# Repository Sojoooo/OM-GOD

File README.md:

<h1 align="center">
  <br>
  OM-GOD
  <br>
</h1>

<h4 align="center">
Ominichord [Gate of Divinity]. Mash-up of all the previous omnichords and more.
</h4>

<div align="center">

</div>

<p align="center">
  <a href="#key-features">Key Features</a> •
  <a href="#design-process">Design Process</a> •
  <a href="#pcb">PCB</a> •
  <a href="#bom">BOM</a> •
  <a href="#journal">Development Journal</a> •
  <a href="#credits">Credits</a> •
  <a href="#license">License</a>
</p>

## Key Features

- **STM32H7 microcontroller** for high-performance processing
- **Texas Instruments DACs and amplifiers** for professional audio quality
- **MIDI connectivity** for external device integration
- **USB-C programming and power delivery**
- **Battery-powered portable design**
- **Cherry MX mechanical switches** for tactile feedback
- **48-button chord matrix** (4 rows × 12 buttons)
- **Rotary encoders** for parameter control
- **LED display** for status and settings

## Design Process

The OM-GOD project began with extensive research into existing omnichord designs and their features. After compiling schematics and manuals, I created a comprehensive feature list to guide the development process.

## PCB

Designed in KiCad with a focus on audio quality and modern features. Notable components:

- **STM32H7** microcontroller with 144 GPIO pins
- **PCM5122PW DAC** for high-quality audio conversion
- **TPA3116D2DAD Class D amplifier** for powerful audio output
- **BQ24610** battery charging circuit for portable operation
- **Multiple voltage regulators** (12V, 15V, 5V, 3.3V)
- **USB-C power delivery** with negotiator circuit
- **NFC antenna** for contactless communication

### Schematic Development

The schematic evolved through multiple iterations, starting with basic component selection and progressing to a complete audio system with power management, I/O interfaces, and user controls.

### Component Integration

Key integration challenges included:

- Audio signal buffering for noise reduction
- Power distribution for multiple voltage rails
- Component placement optimization
- Signal integrity considerations

### PCB

The PCB layout was made to ensure a proper audio quality. All analog traces  and chips are on the bottom layer, while digital traces are on the top. Also, the gnd plane in the inner bottom layer acts as a faraday's cage, not letting them interfier with each other.

### Final Design

The final design incorporates all planned features while maintaining a compact, portable form factor suitable for live performance.

## BOM

| Component  | Source        | Cost (USD)  |
| ---------  | ------        | ----------- |
| PCB        | JLCPCB        | $348.25     |
| SPEAKER    | MERCADO LIBRE | $7.00       |
| FLEX CABLE | MERCADO LIBRE | $4.42       |
| JST CABLE  | MERCADO LIBRE | $5.00       |
| **Total**  |               | **364.67** |

_Note: Speakers, keycaps, and case are already owned components from previous projects._

## Credits

This project uses:

- [KiCad](https://www.kicad.org/) - PCB design
- [STM32](https://www.st.com/en/microcontrollers-microprocessors/stm32h7-series.html) - Microcontroller
- [Texas Instruments](https://www.ti.com/) - Audio and power components
- [Fusion 360](https://www.autodesk.com/products/fusion-360/) - 3D modeling

## License

MIT

---

> GitHub [@Sojooo](https://github.com/Sojooo)

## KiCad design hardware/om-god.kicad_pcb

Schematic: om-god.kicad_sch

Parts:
AUDIO1: PJ-393_C2837065; AUDIO-SMD_PJ-393; LCSC Part C2837065
C1, C2, C3, C7, C12, C17, C34, C35, C36, C37, C38, C39, C81, C188, C196: 2.2uF; C_0402_1005Metric
C4, C5, C6, C8, C9, C10, C11, C13, C14, C15, C16, C18, C40, C42, C43, C44, C45, C50, C51, C52, C53, C54, C55, C59, C60, C61, C62, C63, C75, C76, C79, C80, C83, C84, C124, C126, C127, C130, C133, C134, C138, C139, C141, C147, C150, C152, C153, C156, C158, C163, C198, C199, C200, C201, C202, C203, C206: 0.1uF; C_0402_1005Metric
C19, C20, C21, C22, C23, C24, C25, C26, C27, C28, C29, C30, C31, C32, C33: 10uF; CAP-SMD_BD4.0-L4.3-W4.3-FD
C41, C117: 0.1uF; C_0603_1608Metric
C46, C47: 82nF; C_Rect_L4.0mm_W2.5mm_P2.50mm
C48, C49, C64, C65: 5.6nF; C_Rect_L4.0mm_W2.5mm_P2.50mm
C56, C57: 82nF; C_0603_1608Metric
C58: 100uF; C_0402_1005Metric
C66, C67, C68, C69, C70, C71, C72, C73, C82, C165, C189, C190, C191, C193, C194, C195, C197: 1uF; C_0402_1005Metric
C74: 10nF; C_0402_1005Metric
C77, C85, C86, C87, C88: 1nF; C_0402_1005Metric
C78, C97, C98, C99, C100, C140, C144, C145, C146, C151, C155, C159, C161, C164, C166, C172, C174, C175, C178: 100nF; C_0402_1005Metric
C89, C90, C91, C92, C93, C94, C95, C96, C185, C186, C187: 220nF; C_0402_1005Metric
C101, C102, C103, C104: 220uF; CP_Radial_D8.0mm_P3.50mm
C105, C106, C107, C108: 680nF; C_0603_1608Metric
C109, C110, C111, C112, C113, C114, C115, C116: 1uF; C_0603_1608Metric
C118, C119, C120, C121, C122, C123: 10nF; C_0603_1608Metric
C125: 2.2uF; CP_Radial_D8.0mm_P2.50mm
C128, C136, C148: 1uF; CP_Radial_D5.0mm_P2.00mm
C129, C132: 10uF; C_0402_1005Metric
C131: 0.1uF; CP_Radial_D5.0mm_P2.00mm
C137: 10uF; C_0402_1005Metric; not fitted
C142, C149: 220pF; C_0402_1005Metric
C143, C160, C162, C167: 10uF; CP_Radial_D8.0mm_P3.50mm
C154, C157: 22uF; C_0402_1005Metric
C168, C169: 5.1pF; C_0402_1005Metric
C170, C171: 5.6pF; C_0402_1005Metric
C173: 22pF; C_0402_1005Metric
C176, C177, C179, C180, C181, C184: 10uF; C_0603_1608Metric
C182, C183, C192: 220nF; C_0603_1608Metric
C204, C205, C210: 47pF; C_0402_1005Metric; not fitted
C207, C208, C209: 47pF; C_0603_1608Metric; not fitted
C211, C212, C213, C214, C215, C216, C217, C218, C219, C220, C221, C222, C223, C224, C225, C226, C227, C228, C229, C230, C231, C232, C233, C234: 22uF; C_0603_1608Metric
CN1, CN2: DIN-504B-M10; CONN-TH_DIN-504B-M10; LCSC Part C2939346
Card1: TF PUSH; TF-SMD_TF-PUSH; LCSC Part C393941
D1, D2, D3, D4, D5, D6, D7, D8, D9, D10, D11, D12, D13, D14, D15, D16, D17, D18, D19, D20, D21, D22, D23, D24, D25, D26, D27, D28, D29, D30, D31, D32, D33, D34, D35, D36, D37, D38, D39, D40, D41, D42, D43, D44, D45, D46, D47, D48: 1N4148WS_C917117; SOD-323_L1.8-W1.3-LS2.5-RD; LCSC Part C917117
D49: LED; LED0603-RD; LCSC C5656657
D50: 1N4148WT; D_SOD-523
D51: PESD15VL1BA; D_SOD-323_TVS
D52, D53, D54: LED; LED_0603_1608Metric
D55: BAT54; SOT-23
FPC1: 5034801200; FPC-SMD_5034801200; LCSC Part C587969
J1, J2, J5: PJ-625G; AUDIO-TH_PJ-625G; LCSC Part C309300
J3: Conn_01x13_Pin; PinHeader_1x13_P2.54mm_Vertical
J4: Conn_01x03_Pin; PinHeader_1x03_P2.54mm_Vertical
J6, J10: Conn_01x08_Pin; CONN-TH_B8PS-VH-LF-SN; LCSC C157970
J7, J8, J9, J11: Conn_01x02_Socket; CONN-TH_2P-P5.00_WJ500V-5.08-2P; LCSC C8465
L1, L2, L3, L4, L5, L6: 10uH; IND-SMD_L11.0-W10.5_SL1050-330M
L7: 27uH; IND-SMD_L4.8-W3.4
L8: EXC14CE900U; FILTER-SMD_4P-L0.9-W0.7-P0.50-BL; LCSC Part C178761
L9: 6.8uH; L_6.3x6.3_H3
L10: 8uH; L1206
L11, L15: 6.8uH; IND-SMD_L3.2-W2.5_L3225
L12, L13, L14: 15uH; IND-SMD_L12.3-W12.3
OC1: H11L1; DIP-6_W7.62mm_LongPads
Q1, Q2, Q3: Si7617DN; Vishay_PowerPAK_1212-8_Single
R1, R2, R3, R4, R5, R6: 470K; R_0402_1005Metric
R7, R8, R12, R13, R14, R15, R16, R17, R21, R22, R23, R25, R29, R30, R33, R34, R52, R58, R59, R60, R61, R62, R63, R79, R92, R93, R94, R115, R116: 10K; R_0402_1005Metric
R9, R10, R11, R19, R20, R24, R47, R48, R53, R55, R56, R57, R70, R71, R72: 6K; R_0402_1005Metric
R18: 5K; R_0402_1005Metric
R26: 33; R_0402_1005Metric
R27: 220; R_0402_1005Metric
R28, R84: 10; R_0402_1005Metric
R31, R32, R36, R37, R38, R39, R54, R77, R95, R117: 1K; R_0402_1005Metric
R35: 470; R_0402_1005Metric
R40, R42: 47k; R_0402_1005Metric
R41, R43: 75k; R_0402_1005Metric
R44, R45, R46, R49, R50: 100k; R_0402_1005Metric
R51, R109, R133, R135: 10k; R_0402_1005Metric
R64, R65, R66, R67, R68, R69: 3.3; R_0402_1005Metric
R73: 2; R_0402_1005Metric
R74, R75, R78, R80, R89, R110, R112, R121, R123, R125, R127, R129, R131: 100K; R_0402_1005Metric
R76: 32.4K; R_0402_1005Metric
R81: 22.1K; R_0402_1005Metric
R82, R105: 0.01; R_0402_1005Metric
R83, R87: 1k; R_0402_1005Metric
R85: 200K; R_0402_1005Metric
R86, R104: 1.5K; R_0402_1005Metric
R88: 9.31K; R_0402_1005Metric
R90: NTCG163JF103FT1S; R0603; LCSC Part C406719
R91: 430K; R_0402_1005Metric
R96, R97, R98, R99, R100, R101, R102, R103: 22; R_0402_1005Metric
R106: 49.9; R_0402_1005Metric
R107: 50k; R_0402_1005Metric
R108: 2.61k; R_0402_1005Metric
R111: 500K; R_0402_1005Metric
R113, R114: 0; R_0402_1005Metric
R122: 24.9K; R_0402_1005Metric
R124, R132: 43.2K; R_0402_1005Metric
R126, R128, R130: 9.09K; R_0402_1005Metric
R134: 4.7k; R_0402_1005Metric
SW1, SW2, SW3, SW4, SW6, SW7, SW8, SW9, SW11, SW12, SW13, SW14, SW15, SW16, SW17, SW18, SW21, SW22, SW23, SW24, SW25, SW26, SW27, SW28, SW29, SW30, SW31, SW32, SW35, SW36, SW37, SW38, SW39, SW40, SW41, SW42, SW43, SW44, SW45, SW46, SW47, SW48, SW49, SW50, SW51, SW52, SW53, SW54, SW55, SW56, SW57: TS-1003ST-26; SW-SMD_4P-L12.0-W12.0-P5.00-LS15.4; LCSC Part C455234
SW5, SW10, SW19, SW20, SW33, SW34: RotaryEncoder; SW-TH_EC12EXXXX; LCSC C470684
SW58, SW60: SW_Push; SW_SPST_CK_RS282G05A3
SW59: RotaryEncoder_Switch; SW-TH_EC11E1820402; LCSC C361165
U1, U2, U3: PCM5122PW; TSSOP-28_4.4x9.7mm_P0.65mm
U4, U5, U6, U7, U8, U11, U16, U20, U23: NE5532DR; SOIC-8_L4.9-W3.9-P1.27-LS6.0-BL; LCSC Part C7426
U9, U10, U12, U13, U14: SW-TH_6P-L7.0-W7.0-P2.00_7-7-ZS; LCSC C5379891
U15: TS5A23159RSER; UQFN-10_L2.0-W1.5-P0.50-BL-EP; LCSC Part C138710
U17: TPA6120A2DWP; HSOP-20_L12.8-W7.5-P1.27-LS10.3-BL-EP3.3; LCSC Part C2871054
U18, U19: TPA3116D2DAD_C2865736; HTSSOP-32_L11.0-W6.1-P0.65-LS8.1-BL; LCSC Part C2865736
U21: CY8CMBR3116-LQXIT; QFN-24_L4.0-W4.0-P0.50-BL-EP2.6; LCSC Part C914913
U22, U24: FPC-05F-6PH20; FPC-SMD_6P-P0.50_XUNPU_FPC-05F-6PH20; LCSC C2856796
U25: BQ24610; VQFN-24-1EP_4x4mm_P0.5mm_EP2.45x2.45mm
U26: TPS54202DDC; SOT-23-6
U27: W29N02KVSIAF; TSOP-48_L12.0-W18.4-P0.50-LS20.0-TL; LCSC C2940193
U28: USBLC6-2P6; SOT-666
U29: TUSB422IYFPR; DSBGA-9_L1.4-W1.3-R3-C3-P0.40-BL; LCSC Part C702378
U30, U31: SIS412DN-T1-GE3-ES; PDFN-8_L3.1-W3.1-P0.65-LS3.4-BL; LCSC Part C21713860
U32: CRYSTAL-SMD_4P-L3.2-W2.5-BL_SIT8008BI; LCSC C7294602
U33: HS20HS072RX; OLED-SMD_HS20HS072RX; LCSC Part C5329582
U34, U35, U36, U37, U38, U39: LMR33630ADDAR; ESOP-8_L4.9-W3.9-P1.27-LS6.0-TL-EP; LCSC Part C841384
USB1: TYPE-C 16PIN 2MD(073); USB-C-SMD_TYPE-C-6PIN-2MD-073; LCSC Part C2765186
VQ1: STM32H723ZGT6; LQFP-144_L20.0-W20.0-P0.50-LS22.0-BL; LCSC Part C730146
Y1: 32.768KHz; FC-135R_L3.2-W1.5

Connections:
3.3BATT: C191.2, C210.1, C218.1, C224.1, C230.1, C234.1, J6.8, J10.8, L15.2, R131.2, VQ1.6 (VBAT)
7th: D3.1 (C), D7.1 (C), D11.1 (C), D15.1 (C), D19.1 (C), D23.1 (C), D27.1 (C), D31.1 (C), D35.1 (C), D39.1 (C), D43.1 (C), D47.1 (C), VQ1.37 (PA3)
#CE: U27.9, VQ1.98 (PC8)
#RE: U27.8, VQ1.118 (PD4)
#WE: U27.18, VQ1.119 (PD5)
+3.3V: C5.1, C10.1, C15.1, C21.1, C26.1, C31.1, C58.1, C60.1, C80.1, C82.1, C134.2, C140.1, C141.1, C144.1, C146.1, C150.2, C151.1, C155.1, C159.1, C161.1, C164.1, C165.1, C166.1, C174.1, C175.1, C178.1, C198.2, C205.1, C212.1, C217.1, C223.1, C229.1, Card1.4 (VDD), FPC1.8, FPC1.9, FPC1.11, J6.5, J10.5, L11.2, OC1.6 (VCC), R18.2, R22.1, R23.1, R26.1, R29.2, R33.2, R35.2, R52.1, R58.2, R59.2, R60.2, R61.2, R62.2, R63.2, R75.2, R78.2, R80.2, R83.1, R85.1, R86.2, R87.1, R88.1, R104.1, R113.1, R123.2, SW58.2, SW60.2, U1.17 (MODE1), U1.28 (DVDD), U2.17 (MODE1), U2.28 (DVDD), U3.17 (MODE1), U3.28 (DVDD), U15.8 (VCC), U21.7 (VDD), U27.12, U27.34, U27.37, U27.39, U29.A3 (VDD), VQ1.17 (VDD), VQ1.30 (VDD), VQ1.39 (VDD), VQ1.52 (VDD), VQ1.62 (VDD), VQ1.72 (VDD), VQ1.84 (VDD), VQ1.95 (VDD33USB), VQ1.108 (VDD), VQ1.121 (VDD), VQ1.131 (VDD), VQ1.144 (VDD)
+3.3VA: C4.1, C8.1, C9.1, C13.1, C14.1, C18.1, C19.1, C23.1, C24.1, C28.1, C29.1, C33.1, C172.1, R113.2, R114.1, R114.2, U1.1 (CPVDD), U1.8 (AVDD), U1.25 (XSMT), U2.1 (CPVDD), U2.8 (AVDD), U2.25 (XSMT), U3.1 (CPVDD), U3.8 (AVDD), U3.25 (XSMT), VQ1.32 (VREF+), VQ1.33 (VDDA)
+5V: C204.1, C211.1, C216.1, C222.1, C228.1, J6.6, J10.6, L10.2, R121.2, R134.2
+12V: C41.2, C44.2, C45.2, C52.2, C54.2, C55.2, C61.1, C63.2, C74.1, C76.1, C84.2, C85.2, C86.2, C87.2, C88.2, C97.2, C98.2, C99.2, C100.2, C101.1, C102.1, C103.1, C104.1, C124.2, C129.1, C132.1, C133.1, C137.1, C139.1, C207.1, C208.1, C209.1, C213.1, C214.1, C215.1, C219.1, C220.1, C221.1, C225.1, C226.1, C227.1, C231.1, C232.1, C233.1, J6.1, J6.2, J10.1, J10.2, L12.2, L13.2, L14.2, R45.1, R46.1, R50.2, R125.2, R127.2, R129.2, U4.1 (VCC+), U5.1 (VCC+), U6.1 (VCC+), U7.1 (VCC+), U8.1 (VCC+), U11.1 (VCC+), U16.1 (VCC+), U17.3 (LVCC+), U17.18 (RVCC+), U18.17 (AVCC), U18.18 (PVCC), U18.19 (PVCC), U18.31 (PVCC), U18.32 (PVCC), U19.17 (AVCC), U19.18 (PVCC), U19.19 (PVCC), U19.31 (PVCC), U19.32 (PVCC), U20.1 (VCC+), U23.1 (VCC+), U26.3 (VIN)
+BATT: C158.1, C160.1, C162.1, C173.2, C184.1, C192.1, J11.1, Q3.5 (D), R105.2, R111.1, U25.13 (SRN), U39.2 (VIN), U39.3 (EN)
-12V: C40.2, C42.2, C43.2, C50.2, C51.2, C53.2, C59.2, C62.2, C75.2, C79.2, C117.2, C137.2, C139.2, C153.2, C154.2, C157.2, J6.7, J10.7, R108.1, U4.5 (VCC-), U5.5 (VCC-), U6.5 (VCC-), U7.5 (VCC-), U8.5 (VCC-), U11.5 (VCC-), U16.5 (VCC-), U17.1 (LVCC-), U17.20 (RVCC-), U20.5 (VCC-), U23.5 (VCC-), U26.1 (GND)
ALE: U27.17, VQ1.81 (PD12)
BCK HEADPHONE: U1.21 (BCK), VQ1.69 (PB10)
BCK SPEAKER: U2.21 (BCK), VQ1.41 (PA5)
BCK STEREO OUT: U3.21 (BCK), VQ1.133 (PB3)
CLE: U27.16, VQ1.80 (PD11)
Chord A: SW1.3, SW1.4, SW2.3, SW2.4, SW3.3, SW3.4, SW4.3, SW4.4, VQ1.7 (PC13)
Chord Ab: SW51.3, SW51.4, SW52.3, SW52.4, SW53.3, SW53.4, SW54.3, SW54.4, VQ1.28 (PC2_C)
Chord B: SW11.3, SW11.4, SW12.3, SW12.4, SW13.3, SW13.4, SW14.3, SW14.4, VQ1.13 (PF3)
Chord Bb: SW6.3, SW6.4, SW7.3, SW7.4, SW8.3, SW8.4, SW9.3, SW9.4, VQ1.12 (PF2)
Chord C: SW15.3, SW15.4, SW16.3, SW16.4, SW17.3, SW17.4, SW18.3, SW18.4, VQ1.14 (PF4)
Chord D: SW25.3, SW25.4, SW26.3, SW26.4, SW27.3, SW27.4, SW28.3, SW28.4, VQ1.18 (PF6)
Chord Db: SW21.3, SW21.4, SW22.3, SW22.4, SW23.3, SW23.4, SW24.3, SW24.4, VQ1.15 (PF5)
Chord E: SW35.3, SW35.4, SW36.3, SW36.4, SW37.3, SW37.4, SW38.3, SW38.4, VQ1.20 (PF8)
Chord Eb: SW29.3, SW29.4, SW30.3, SW30.4, SW31.3, SW31.4, SW32.3, SW32.4, VQ1.19 (PF7)
Chord F: SW39.3, SW39.4, SW40.3, SW40.4, SW41.3, SW41.4, SW42.3, SW42.4, VQ1.21 (PF9)
Chord G: SW47.3, SW47.4, SW48.3, SW48.4, SW49.3, SW49.4, SW50.3, SW50.4, VQ1.26 (PC0)
Chord Gb: SW43.3, SW43.4, SW44.3, SW44.4, SW45.3, SW45.4, SW46.3, SW46.4, VQ1.22 (PF10)
Chords Volume Encoder A: SW19.A, VQ1.127 (PG12)
Chords Volume Encoder B: SW19.B, VQ1.126 (PG11)
DIN HEADPHONE: U1.22 (DIN), VQ1.27 (PC1)
DIN SPEAKER: U2.22 (DIN), VQ1.43 (PA7)
DIN STEREO OUT: U3.22 (DIN), VQ1.48 (PB2)
DN USB: L8.1, U24.5
DN USB 2: U22.5, VQ1.103 (PA11)
DP USB: L8.2, U24.6
DP USB 2: U22.6, VQ1.104 (PA12)
Extention: D4.1 (C), D8.1 (C), D12.1 (C), D16.1 (C), D20.1 (C), D24.1 (C), D28.1 (C), D32.1 (C), D36.1 (C), D40.1 (C), D44.1 (C), D48.1 (C), VQ1.42 (PA6)
Func Encoder A: SW59.A, VQ1.87 (PG2)
Func Encoder B: SW59.B, VQ1.82 (PD13)
Func Switch: SW59.S1, VQ1.79 (PD10)
GND: AUDIO1.4, C4.2, C5.2, C6.1, C7.1, C8.2, C9.2, C10.2, C11.1, C12.1, C13.2, C14.2, C15.2, C16.1, C17.1, C18.2, C19.2, C20.2, C21.2, C22.2, C23.2, C24.2, C25.2, C26.2, C27.2, C28.2, C29.2, C30.2, C31.2, C32.2, C33.2, C34.2, C35.2, C36.2, C37.2, C38.2, C39.2, C40.1, C41.1, C42.1, C43.1, C44.1, C45.1, C48.1, C49.1, C50.1, C51.1, C52.1, C53.1, C54.1, C55.1, C56.1, C57.1, C58.2, C59.1, C60.2, C61.2, C62.1, C63.1, C66.2, C67.2, C74.2, C75.1, C76.2, C77.2, C78.1, C79.1, C80.2, C81.2, C82.2, C83.2, C84.1, C85.1, C86.1, C87.1, C88.1, C97.1, C98.1, C99.1, C100.1, C101.2, C102.2, C103.2, C104.2, C105.1, C106.2, C107.1, C108.2, C109.1, C110.2, C111.1, C112.2, C113.1, C114.2, C115.1, C116.2, C117.1, C118.1, C119.2, C120.1, C121.2, C122.1, C123.2, C124.1, C125.2, C127.1, C128.2, C129.2, C131.2, C132.2, C133.2, C134.1, C136.2, C138.2, C140.2, C141.2, C142.2, C143.2, C144.2, C145.2, C146.2, C148.2, C149.2, C150.1, C151.2, C153.1, C154.1, C155.2, C156.2, C157.1, C159.2, C160.2, C161.2, C162.2, C164.2, C165.2, C166.2, C167.2, C168.1, C169.1, C170.1, C171.1, C172.2, C174.2, C175.2, C176.2, C177.2, C178.2, C179.2, C180.2, C181.2, C182.2, C183.2, C184.2, C185.2, C186.2, C187.2, C188.2, C189.2, C190.2, C191.1, C192.2, C193.2, C194.2, C195.2, C196.2, C197.2, C198.1, C211.2, C212.2, C213.2, C214.2, C215.2, C216.2, C217.2, C218.2, C219.2, C220.2, C221.2, C222.2, C223.2, C224.2, C225.2, C226.2, C227.2, C228.2, C229.2, C230.2, C231.2, C232.2, C233.2, C234.2, CN1.6, CN1.7, CN2.2, CN2.6, CN2.7, Card1.6 (VSS), Card1.10, Card1.11, Card1.12, Card1.13, D49.1 (K), D51.1 (K), FPC1.1, FPC1.10, FPC1.12, FPC1.13, FPC1.14, J1.2, J2.2, J5.2, J6.3, J6.4, J10.3, J10.4, J11.2, L7.2, OC1.5 (GND), R10.2, R12.1, R14.1, R20.2, R30.1, R34.1, R36.1, R37.1, R41.2, R43.2, R44.2, R49.2, R53.2, R55.2, R70.2, R76.2, R79.2, R81.2, R90.2, R91.2, R106.2, R109.1, R112.2, R122.1, R124.1, R126.1, R128.1, R130.1, R132.1, R133.1, R135.1, SW5.C, SW10.C, SW19.C, SW20.C, SW33.C, SW34.C, SW55.1, SW55.2, SW56.3, SW56.4, SW57.3, SW57.4, SW59.C, SW59.S2, U1.3 (CPGND), U1.9 (AGND), U1.16 (ADR2/GPIO2/DOUT), U1.18 (MODE2/MS), U1.24 (ADR1/MISO/FMT), U1.27 (DGND), U2.3 (CPGND), U2.9 (AGND), U2.16 (ADR2/GPIO2/DOUT), U2.18 (MODE2/MS), U2.24 (ADR1/MISO/FMT), U2.27 (DGND), U3.3 (CPGND), U3.9 (AGND), U3.16 (ADR2/GPIO2/DOUT), U3.18 (MODE2/MS), U3.24 (ADR1/MISO/FMT), U3.27 (DGND), U4.4 (IN2+), U4.6 (IN1+), U8.4 (IN2+), U8.6 (IN1+), U9.5, U10.5, U12.5, U13.1, U14.1, U15.3 (GND), U17.21 (EP), U18.1 (MODSEL), U18.9 (GND), U18.13 (AM2), U18.14 (AM1), U18.15 (AM0), U18.22 (GND), U18.25 (GND), U18.28 (GND), U18.33 (PAD), U19.1 (MODSEL), U19.9 (GND), U19.10 (LINP), U19.11 (LINN), U19.13 (AM2), U19.14 (AM1), U19.15 (AM0), U19.22 (GND), U19.25 (GND), U19.28 (GND), U19.33 (PAD), U21.8 (VSS), U21.25 (EP), U22.4, U22.7, U22.8, U23.6 (IN1+), U24.4, U24.7, U24.8, U25.17 (GND), U25.25 (GND), U27.13, U27.25, U27.36, U27.48, U28.2 (GND), U29.C2 (GND), U30.1 (S), U30.2 (S), U30.3 (S), U32.2, U32.4, U34.1 (PGND), U34.9 (EP), U35.1 (PGND), U35.9 (EP), U36.1 (PGND), U36.9 (EP), U37.1 (PGND), U37.9 (EP), U38.1 (PGND), U38.9 (EP), U39.1 (PGND), U39.9 (EP), USB1.1 (GND), USB1.12 (GND), USB1.13 (SHELL), USB1.14 (SHELL), VQ1.16 (VSS), VQ1.31 (VSSA), VQ1.38 (VSS), VQ1.51 (VSS), VQ1.61 (VSS), VQ1.83 (VSS), VQ1.94 (VSS), VQ1.107 (VSS), VQ1.120 (VSS), VQ1.130 (VSS)
GPIO3 HEADPHONE: U1.15 (GPIO3/AGNS), VQ1.49 (PF11)
GPIO3 SPEAKER: U2.15 (GPIO3/AGNS), VQ1.57 (PG1)
GPIO3 STEREO OUT: U3.15 (GPIO3/AGNS), VQ1.44 (PC4)
GPIO4 HEADPHONE: U1.14 (GPIO4/MAST), VQ1.50 (PF12)
GPIO4 SPEAKER: U2.14 (GPIO4/MAST), VQ1.64 (PE11)
GPIO4 STEREO OUT: U3.14 (GPIO4/MAST), VQ1.45 (PC5)
GPIO5 HEADPHONE: U1.13 (GPIO5/ATT0), VQ1.53 (PF13)
GPIO5 SPEAKER: U2.13 (GPIO5/ATT0), VQ1.65 (PE12)
GPIO5 STEREO OUT: U3.13 (GPIO5/ATT0), VQ1.46 (PB0)
GPIO6 HEADPHONE: U1.19 (GPIO6/FLT), VQ1.56 (PG0)
GPIO6 SPEAKER: U2.19 (GPIO6/FLT), VQ1.66 (PE13)
GPIO6 STEREO OUT: U3.19 (GPIO6/FLT), VQ1.47 (PB1)
HEADPHONE AMP L: AUDIO1.2, R117.2, U17.2 (LOUT)
HEADPHONE AMP R: AUDIO1.3, R54.1, U17.19 (ROUT)
HEADPHONE BUFF L N: R11.1, R32.2, U5.2 (OUT2)
HEADPHONE BUFF L P: R9.2, R31.1, U5.7 (IN1-), U5.8 (OUT1)
HEADPHONE BUFF R N: R24.1, R39.2, U11.2 (OUT2)
HEADPHONE BUFF R P: R19.2, R38.1, U11.7 (IN1-), U11.8 (OUT1)
HEADPHONE DAC L: C34.1, R1.2, U5.6 (IN1+)
HEADPHONE DAC R: C35.1, R2.2, U11.6 (IN1+)
HEADPHONE GPIO L: AUDIO1.6, R29.1, VQ1.67 (PE14)
HEADPHONE GPIO R: AUDIO1.7, R33.1, VQ1.68 (PE15)
INT_N USB: R85.2, U24.3, U29.B2 (INT_N)
INT_N USB 2: U22.3, VQ1.102 (PA10)
IO0: R103.2, VQ1.85 (PD14)
IO1: R102.2, VQ1.86 (PD15)
IO2: R101.2, VQ1.114 (PD0)
IO3: R100.2, VQ1.115 (PD1)
IO4: R99.2, VQ1.58 (PE7)
IO5: R98.2, VQ1.59 (PE8)
IO6: R97.2, VQ1.60 (PE9)
IO7: R96.2, VQ1.63 (PE10)
IOFF 13: J4.1, U21.11 (CS13/GPO5)
IOFF 14: J4.2, U21.10 (CS14/GPO6)
IOFF 15: J4.3, U21.9 (CS15/SH/~HI)
Keyboard Volume Encoder A: SW33.A, VQ1.129 (PG14)
Keyboard Volume Encoder B: SW33.B, VQ1.128 (PG13)
LCD CS: FPC1.2, VQ1.3 (PE4)
LCD RESET: FPC1.6, VQ1.2 (PE3)
LCD RS: FPC1.3, VQ1.4 (PE5)
LCD SCL: FPC1.4, VQ1.1 (PE2)
LCD SDA: FPC1.5, VQ1.5 (PE6)
LRCK HEADPHONE: U1.23 (LRCK), VQ1.73 (PB12)
LRCK SPEAKER: U2.23 (LRCK), VQ1.110 (PA15)
LRCK STEREO OUT: U3.23 (LRCK), VQ1.40 (PA4)
MONO BUFF: R116.1, U8.8 (OUT1), U15.9 (NC1)
MUTE SUB: R49.1, U19.12 (MUTE), VQ1.140 (PB9)
MUTE TWEET/WOOF: R44.1, U18.12 (MUTE), VQ1.142 (PE1)
Main On/Off Switch: U9.6, VQ1.105 (PA13)
Main Volume Encoder A: SW5.A, VQ1.139 (PB8)
Main Volume Encoder B: SW5.B, VQ1.132 (PG15)
Mayor: D1.1 (C), D5.1 (C), D9.1 (C), D13.1 (C), D17.1 (C), D21.1 (C), D25.1 (C), D29.1 (C), D33.1 (C), D37.1 (C), D41.1 (C), D45.1 (C), VQ1.29 (PC3_C)
Metronome On/Off Switch: U14.2, VQ1.100 (PA8)
Minor: D2.1 (C), D6.1 (C), D10.1 (C), D14.1 (C), D18.1 (C), D22.1 (C), D26.1 (C), D30.1 (C), D34.1 (C), D38.1 (C), D42.1 (C), D46.1 (C), VQ1.36 (PA2)
unnamed: C46.2, C47.1, R12.2
unnamed: C56.2, R21.1, R25.2
unnamed: C64.1, C65.2, R34.2
unnamed: C78.2, R50.1
unnamed: C118.2, R64.2
unnamed: C119.1, R65.1
unnamed: C120.2, R66.2
unnamed: C121.1, R67.1
unnamed: C122.2, R68.2
unnamed: C123.1, R69.1
unnamed: C125.1, R73.1
unnamed: C188.1, C196.1, VQ1.71 (VCAP), VQ1.106 (VCAP)
unnamed: CN1.4, R27.2
unnamed: CN1.5, D50.2 (A), OC1.2
unnamed: CN2.4, R26.2
unnamed: CN2.5, R28.2
unnamed: D1.2 (A), SW1.1, SW1.2
unnamed: D2.2 (A), SW2.1, SW2.2
unnamed: D3.2 (A), SW3.1, SW3.2
unnamed: D4.2 (A), SW4.1, SW4.2
unnamed: D5.2 (A), SW6.1, SW6.2
unnamed: D6.2 (A), SW7.1, SW7.2
unnamed: D7.2 (A), SW8.1, SW8.2
unnamed: D8.2 (A), SW9.1, SW9.2
unnamed: D9.2 (A), SW11.1, SW11.2
unnamed: D10.2 (A), SW12.1, SW12.2
unnamed: D11.2 (A), SW13.1, SW13.2
unnamed: D12.2 (A), SW14.1, SW14.2
unnamed: D13.2 (A), SW15.1, SW15.2
unnamed: D14.2 (A), SW16.1, SW16.2
unnamed: D15.2 (A), SW17.1, SW17.2
unnamed: D16.2 (A), SW18.1, SW18.2
unnamed: D17.2 (A), SW21.1, SW21.2
unnamed: D18.2 (A), SW22.1, SW22.2
unnamed: D19.2 (A), SW23.1, SW23.2
unnamed: D20.2 (A), SW24.1, SW24.2
unnamed: D21.2 (A), SW25.1, SW25.2
unnamed: D22.2 (A), SW26.1, SW26.2
unnamed: D23.2 (A), SW27.1, SW27.2
unnamed: D24.2 (A), SW28.1, SW28.2
unnamed: D25.2 (A), SW29.1, SW29.2
unnamed: D26.2 (A), SW30.1, SW30.2
unnamed: D27.2 (A), SW31.1, SW31.2
unnamed: D28.2 (A), SW32.1, SW32.2
unnamed: D29.2 (A), SW35.1, SW35.2
unnamed: D30.2 (A), SW36.1, SW36.2
unnamed: D31.2 (A), SW37.1, SW37.2
unnamed: D32.2 (A), SW38.1, SW38.2
unnamed: D33.2 (A), SW39.1, SW39.2
unnamed: D34.2 (A), SW40.1, SW40.2
unnamed: D35.2 (A), SW41.1, SW41.2
unnamed: D36.2 (A), SW42.1, SW42.2
unnamed: D37.2 (A), SW43.1, SW43.2
unnamed: D38.2 (A), SW44.1, SW44.2
unnamed: D39.2 (A), SW45.1, SW45.2
unnamed: D40.2 (A), SW46.1, SW46.2
unnamed: D41.2 (A), SW47.1, SW47.2
unnamed: D42.2 (A), SW48.1, SW48.2
unnamed: D43.2 (A), SW49.1, SW49.2
unnamed: D44.2 (A), SW50.1, SW50.2
unnamed: D45.2 (A), SW51.1, SW51.2
unnamed: D46.2 (A), SW52.1, SW52.2
unnamed: D47.2 (A), SW53.1, SW53.2
unnamed: D48.2 (A), SW54.1, SW54.2
unnamed: D49.2 (A), U9.2
unnamed: D50.1 (K), OC1.1, R27.1
unnamed: D52.2 (A), R92.1
unnamed: D52.1 (K), U25.5 (STAT1)
unnamed: D53.2 (A), R93.1
unnamed: D53.1 (K), U25.9 (STAT2)
unnamed: D54.2 (A), R94.1
unnamed: D54.1 (K), U25.8 (~PG)
unnamed: C148.1, D55.1 (A), U25.18 (REGN)
unnamed: C152.1, D55.3 (K), U25.22 (BTST)
unnamed: L8.3, U28.6 (I/O1)
unnamed: L8.4, U28.4 (I/O2)
unnamed: C126.2, Q1.4 (G), Q2.4 (G), R74.2, R77.1
unnamed: C126.1, Q1.1 (S), Q1.2 (S), Q1.3 (S), Q2.5 (D), R74.1, R84.1
unnamed: C163.1, Q3.4 (G), R95.2, R110.2
unnamed: R18.1, U9.3
unnamed: R83.2, U27.19
unnamed: R88.2, R89.1, R90.1, R91.1
unnamed: R96.1, U27.44
unnamed: R97.1, U27.43
unnamed: R98.1, U27.42
unnamed: R99.1, U27.41
unnamed: R100.1, U27.32
unnamed: R101.1, U27.31
unnamed: R102.1, U27.30
unnamed: R103.1, U27.29
unnamed: R106.1, R107.2
unnamed: C1.2, U1.4 (CAPM)
unnamed: C1.1, U1.2 (CAPP)
unnamed: C6.2, C22.1, U1.26 (LDOO)
unnamed: R1.1, U1.6 (OUTL)
unnamed: R2.1, U1.7 (OUTR)
unnamed: C20.1, U1.10 (VCOM/DEMP)
unnamed: C7.2, U1.5 (VNEG)
unnamed: C2.2, U2.4 (CAPM)
unnamed: C2.1, U2.2 (CAPP)
unnamed: C11.2, C27.1, U2.26 (LDOO)
unnamed: R3.1, U2.6 (OUTL)
unnamed: R4.1, U2.7 (OUTR)
unnamed: C25.1, U2.10 (VCOM/DEMP)
unnamed: C12.2, U2.5 (VNEG)
unnamed: C3.2, U3.4 (CAPM)
unnamed: C3.1, U3.2 (CAPP)
unnamed: C16.2, C32.1, U3.26 (LDOO)
unnamed: R5.1, U3.6 (OUTL)
unnamed: R6.1, U3.7 (OUTR)
unnamed: C30.1, U3.10 (VCOM/DEMP)
unnamed: C17.2, U3.5 (VNEG)
unnamed: R7.2, R8.1, R115.2, U4.7 (IN1-)
unnamed: U4.2 (OUT2), U4.3 (IN2-)
unnamed: R10.1, U5.4 (IN2+)
unnamed: R9.1, R11.2, U5.3 (IN2-)
unnamed: C47.2, R14.2, U7.6 (IN1+)
unnamed: R13.2, U7.7 (IN1-), U7.8 (OUT1)
unnamed: C48.2, C49.2, R13.1, R15.1, R15.2, U7.4 (IN2+)
unnamed: R16.2, R17.1, R116.2, U8.7 (IN1-)
unnamed: U8.2 (OUT2), U8.3 (IN2-)
unnamed: R20.1, U11.4 (IN2+)
unnamed: R19.1, R24.2, U11.3 (IN2-)
unnamed: C57.2, R25.1, U16.6 (IN1+)
unnamed: C64.2, R30.2, U16.4 (IN2+)
unnamed: R31.2, R36.2, U17.4 (LIN+)
unnamed: R32.1, R117.1, U17.5 (LIN-)
unnamed: R37.2, R38.2, U17.17 (RIN+)
unnamed: R39.1, R54.2, U17.16 (RIN-)
unnamed: C92.1, U18.20 (BSNL)
unnamed: C90.2, U18.26 (BSNR)
unnamed: C91.2, U18.24 (BSPL)
unnamed: C89.2, U18.30 (BSPR)
unnamed: R40.2, R41.1, U18.8 (GAIN/SLV)
unnamed: C66.1, R40.1, U18.6 (PLIMIT), U18.7 (GVDD)
unnamed: C71.1, U18.11 (LINN)
unnamed: C70.1, U18.10 (LINP)
unnamed: C92.2, L4.1, U18.21 (OUTNL)
unnamed: C90.1, L2.1, U18.27 (OUTNR)
unnamed: C91.1, L3.1, U18.23 (OUTPL)
unnamed: C89.1, L1.1, U18.29 (OUTPR)
unnamed: C69.1, U18.5 (RINN)
unnamed: C68.1, U18.4 (RINP)
unnamed: R51.1, U18.16 (SYNC)
unnamed: C96.1, U19.20 (BSNL)
unnamed: C94.2, U19.26 (BSNR)
unnamed: C95.2, U19.24 (BSPL)
unnamed: C93.2, U19.30 (BSPR)
unnamed: R42.2, R43.1, U19.8 (GAIN/SLV)
unnamed: C67.1, R42.1, U19.6 (PLIMIT), U19.7 (GVDD)
unnamed: C95.1, C96.2, L6.1, U19.21 (OUTNL), U19.23 (OUTPL)
unnamed: C93.1, C94.1, L5.1, U19.27 (OUTNR), U19.29 (OUTPR)
unnamed: C73.1, U19.5 (RINN)
unnamed: C72.1, U19.4 (RINP)
unnamed: C77.1, R51.2, U19.16 (SYNC)
unnamed: R53.1, U20.6 (IN1+)
unnamed: R47.2, R48.1, U20.7 (IN1-)
unnamed: R55.1, U20.4 (IN2+)
unnamed: R56.2, R57.1, U20.3 (IN2-)
unnamed: C81.1, U21.5 (CMOD)
unnamed: C83.1, U21.6 (VCC)
unnamed: U23.7 (IN1-), U23.8 (OUT1)
unnamed: R70.1, U23.4 (IN2+)
unnamed: R71.2, R72.1, U23.3 (IN2-)
unnamed: C127.2, C130.1, Q2.1 (S), Q2.2 (S), Q2.3 (S), R82.1, U25.2 (ACP)
unnamed: R75.1, R76.1, U25.16 (ACSET)
unnamed: C128.1, U25.4 (CE), U25.10 (VREF)
unnamed: U25.21 (HIDRV), U31.4 (G)
unnamed: R80.1, R81.1, U25.11 (ISET1)
unnamed: R78.1, R79.1, U25.15 (ISET2)
unnamed: U25.19 (LODRV), U30.4 (G)
unnamed: C152.2, L9.1, U25.20 (PH), U30.5 (D), U30.6 (D), U30.7 (D), U30.8 (D), U30.9 (D), U31.1 (S), U31.2 (S), U31.3 (S)
unnamed: C156.1, C158.2, L9.2, R105.1, U25.14 (SRP)
unnamed: C138.1, R89.2, U25.6 (TS)
unnamed: C131.1, U25.7 (TTC)
unnamed: C136.1, R84.2, U25.24 (VCC)
unnamed: C173.1, R111.2, R112.1, U25.12 (VFB)
unnamed: R77.2, U25.3 (~ACDRV)
unnamed: R95.1, U25.23 (~BATDRV)
unnamed: C147.2, U26.6 (BOOT)
unnamed: R107.1, R108.2, U26.4 (FB)
unnamed: C147.1, L7.1, U26.2 (SW)
unnamed: C149.1, U29.C1 (CC1), USB1.4 (CC1)
unnamed: C142.1, U29.A1 (CC2), USB1.10 (CC2)
unnamed: C199.2, U34.7 (BOOT)
unnamed: C204.2, R121.1, R122.2, U34.5 (FB)
unnamed: C199.1, L10.1, U34.8 (SW)
unnamed: C189.1, U34.6 (VCC)
unnamed: C200.2, U35.7 (BOOT)
unnamed: C205.2, R123.1, R124.2, U35.5 (FB)
unnamed: C200.1, L11.1, U35.8 (SW)
unnamed: C190.1, U35.6 (VCC)
unnamed: C201.2, U36.7 (BOOT)
unnamed: C207.2, R125.1, R126.2, U36.5 (FB)
unnamed: C201.1, L13.1, U36.8 (SW)
unnamed: C193.1, U36.6 (VCC)
unnamed: C202.2, U37.7 (BOOT)
unnamed: C208.2, R127.1, R128.2, U37.5 (FB)
unnamed: C202.1, L14.1, U37.8 (SW)
unnamed: C194.1, U37.6 (VCC)
unnamed: C203.2, U38.7 (BOOT)
unnamed: C209.2, R129.1, R130.2, U38.5 (FB)
unnamed: C203.1, L12.1, U38.8 (SW)
unnamed: C195.1, U38.6 (VCC)
unnamed: C206.2, U39.7 (BOOT)
unnamed: C210.2, R131.1, R132.2, U39.5 (FB)
unnamed: C206.1, L15.1, U39.8 (SW)
unnamed: C197.1, U39.6 (VCC)
unnamed: U28.3 (I/O2), USB1.5 (DN2), USB1.7 (DN1)
unnamed: U28.1 (I/O1), USB1.6 (DP1), USB1.8 (DP2)
unnamed: R133.2, SW60.1, VQ1.138 (BOOT0)
unnamed: R109.2, SW58.1, VQ1.25 (NRST)
unnamed: R134.1, R135.2, VQ1.101 (PA9)
unnamed: C168.2, VQ1.8 (PC14-OSC32_IN), Y1.2
unnamed: C169.2, VQ1.9 (PC15-OSC32_OUT), Y1.1
unnamed: C170.2, U32.3, VQ1.23 (PH0-OSC_IN)
unnamed: C171.2, U32.1, VQ1.24 (PH1-OSC_OUT)
Next Chord Switch: SW56.1, SW56.2, VQ1.88 (PG3)
Octave Down Switch: SW57.1, SW57.2, VQ1.89 (PG4)
Octave Up Switch: SW55.3, SW55.4, VQ1.90 (PG5)
PEDAL GPIO: J5.6, R52.2, VQ1.77 (PD8)
RX MIDI: OC1.4, R35.1, VQ1.35 (PA1)
RY/#BY: R87.2, U27.7, VQ1.96 (PC6)
Recording Mode Switch: U12.6, VQ1.91 (PG6)
Rythm On/Off Switch: U13.2, VQ1.93 (PG8)
Rythm Volume Encoder A: SW10.A, VQ1.117 (PD3)
Rythm Volume Encoder B: SW10.B, VQ1.109 (PA14)
SCL I2C1: R86.1, U2.12 (SCL/MC/ATT1), U21.22 (I2CSCL), U22.2, U29.B3 (SCL), VQ1.136 (PB6)
SCL I2C2: U1.12 (SCL/MC/ATT1), VQ1.11 (PF1)
SCL I2C4: U3.12 (SCL/MC/ATT1), VQ1.54 (PF14)
SCL USB: U24.2
SD CD: Card1.9 (CD), R63.1, VQ1.75 (PB14)
SD CLX: Card1.5 (CLX), VQ1.113 (PC12)
SD CMD: Card1.3 (CMD), R60.1, VQ1.116 (PD2)
SD D0: Card1.7 (DAT0), R61.1, VQ1.74 (PB13)
SD D1: Card1.8 (DAT1), R62.1, VQ1.99 (PC9)
SD D2: Card1.1 (DAT2), R58.1, VQ1.111 (PC10)
SD D3: Card1.2 (CD/DAT3), R59.1, VQ1.112 (PC11)
SDA I2C1: R104.2, U2.11 (SDA/MOSI/ATT2), U21.21 (I2CSDA), U22.1, U29.C3 (SDA), VQ1.137 (PB7)
SDA I2C2: U1.11 (SDA/MOSI/ATT2), VQ1.10 (PF0)
SDA I2C4: U3.11 (SDA/MOSI/ATT2), VQ1.55 (PF15)
SDA USB: U24.1
SPEAKER DAC L: C36.1, R3.2, R7.1
SPEAKER DAC R: C37.1, R4.2, R8.2
SPEAKER SUM BUFF: C46.1, C65.1, R21.2, R115.1, U4.8 (OUT1)
SS 0: J3.1, U21.1 (CS0/PS0)
SS 1: J3.2, U21.2 (CS1/PS1)
SS 2: J3.3, U21.3 (CS2/GUARD)
SS 3: J3.4, U21.4 (CS3)
SS 4: J3.5, U21.20 (CS4)
SS 5: J3.6, U21.19 (CS5)
SS 6: J3.7, U21.18 (CS6)
SS 7: J3.8, U21.17 (CS7)
SS 8: J3.9, U21.16 (CS8/GPO0)
SS 9: J3.10, U21.15 (CS9/GPO1)
SS 10: J3.11, U21.14 (CS10/GPO2)
SS 11: J3.12, U21.13 (CS11/GPO3)
SS 12: J3.13, U21.12 (CS12/GPO4)
SS XRES GPIO: U21.24 (~XRES), VQ1.76 (PB15)
STEREO BUFF L: U6.7 (IN1-), U6.8 (OUT1), U15.2 (NO1)
STEREO BUFF L/MONO: J2.6, U15.10 (COM1)
STEREO BUFF R: J1.6, U6.2 (OUT2), U6.3 (IN2-)
STEREO DAC L: R16.1, U6.6 (IN1+)
STEREO DAC R: R17.2, U6.4 (IN2+)
STEREO GPIO L/MONO: J2.7, R23.2, VQ1.134 (PB4)
STEREO GPIO R: J1.7, R22.2, VQ1.135 (PB5)
STEREO OUT DAC L: C38.1, R5.2
STEREO OUT DAC R: C39.1, R6.2
STEREO/MONO GPIO: U15.1 (IN1), VQ1.78 (PD9)
SUB AMP N: C110.1, C116.1, J9.2, L6.2, R69.2
SUB AMP P: C109.2, C115.2, J9.1, L5.2, R68.1
SUB SUM BUFF: C72.2, R57.2, U16.7 (IN1-), U16.8 (OUT1)
SUB SUM BUFF N: C73.2, R56.1, U20.2 (OUT2)
SYS: C130.2, C143.1, C163.2, C167.1, C177.1, C179.1, C180.1, C181.1, C183.1, C185.1, C186.1, C187.1, Q3.1 (S), Q3.2 (S), Q3.3 (S), R82.2, R110.1, U25.1 (ACN), U31.5 (D), U31.6 (D), U31.7 (D), U31.8 (D), U31.9 (D), U35.2 (VIN), U35.3 (EN), U36.2 (VIN), U36.3 (EN), U37.2 (VIN), U37.3 (EN), U38.2 (VIN), U38.3 (EN)
Sustain On/Off Switch: U10.6, VQ1.92 (PG7)
TWEET AMP N: C106.1, C112.1, J8.1, L2.2, R65.2
TWEET AMP P: C105.2, C111.2, J8.2, L1.2, R64.1
TWEET SUM BUFF: C68.2, R48.2, U16.2 (OUT2), U16.3 (IN2-)
TWEET SUM BUFF N: C69.2, R47.1, U20.8 (OUT1)
TX MIDI: R28.1, VQ1.34 (PA0)
Touch Pad Volume Encoder A: SW20.A, VQ1.125 (PG10)
Touch Pad Volume Encoder B: SW20.B, VQ1.124 (PG9)
VBUS: C145.1, C176.1, C182.1, D51.2 (A), Q1.5 (D), R73.2, R92.2, R93.2, R94.2, U28.5 (VBUS), U29.A2 (VBUSIN), U34.2 (VIN), U34.3 (EN), USB1.2 (VBUS), USB1.11 (VBUS)
Vibrato Encoder A: SW34.A, VQ1.123 (PD7)
Vibrato Encoder B: SW34.B, VQ1.122 (PD6)
WOOF AMP N: C108.1, C114.1, J7.2, L4.2, R67.2
WOOF AMP P: C107.2, C113.2, J7.1, L3.2, R66.1
WOOF SUM BUFF: C70.2, R72.2, U7.2 (OUT2), U7.3 (IN2-)
WOOF SUM BUFF N: C71.2, R71.1, U23.2 (OUT2)
/SD SUB: R46.2, U19.2 (SDZ), U19.3 (FAULTZ), VQ1.141 (PE0)
/SD TWEET/WOOF: R45.2, U18.2 (SDZ), U18.3 (FAULTZ), VQ1.143 (PDR_ON)

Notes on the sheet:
Main Knobs
Pedal
Audio Out
Next Chord
Octave Down
Function Knob
Sonic Strings
Advanced Functionalities
Sustain Chord
On/Off
Rythm Volume
I/O
Main Volume
Headphones Out
Metronome
Main
Octave Up
Keyboard Volume
Recording Mode
Main Buttons
Volume
Connect int a gpio exti
Chords Volume
Vibrato Knob
Chord Matrix
Touch Pad Volume
Rythm
Instant Off
Power Managment
Stereo Out
Recording

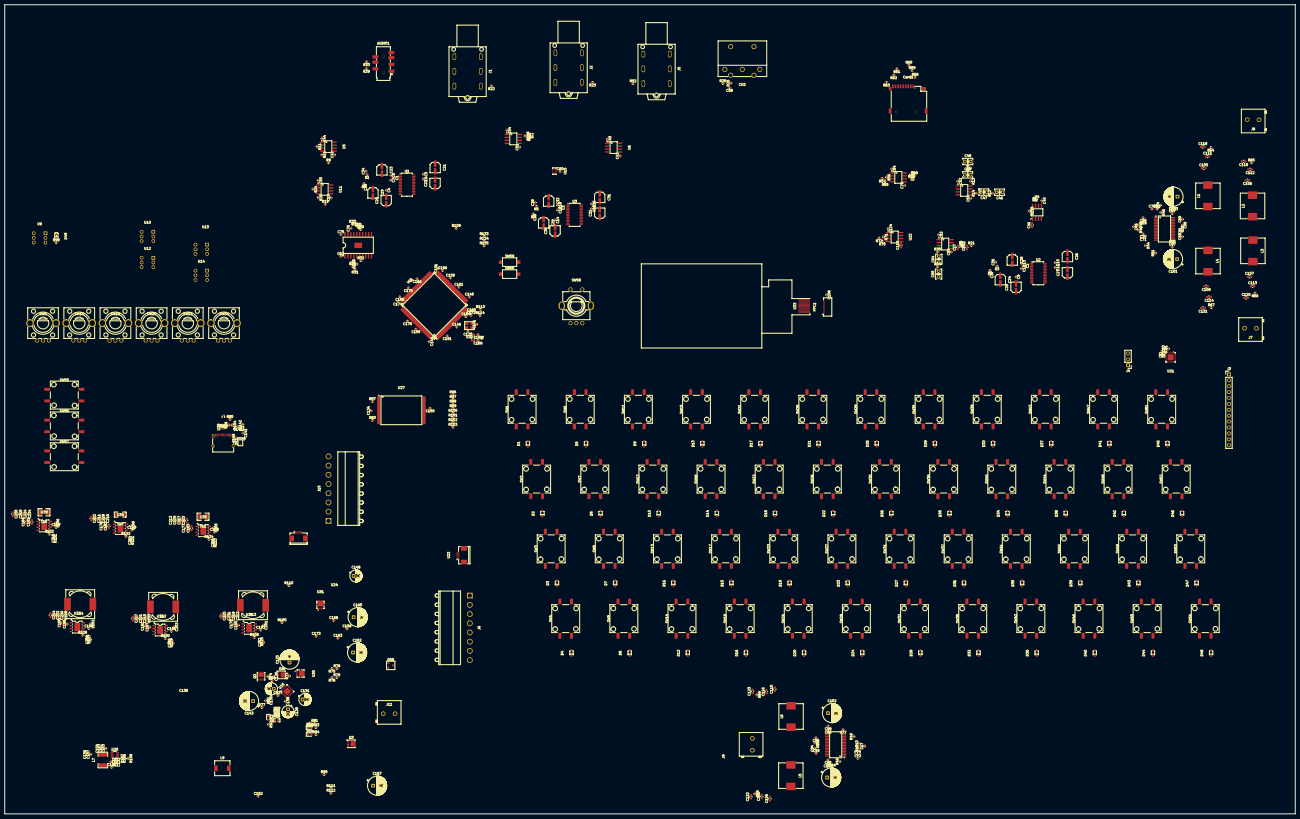
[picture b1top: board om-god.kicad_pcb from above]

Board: 4 copper layers, 554.9 x 347.9 mm, 552 parts (0 on the bottom side), 380 nets, no tracks yet.

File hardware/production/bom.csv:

Designator,Footprint,Quantity,Value,LCSC Part #
AUDIO1,AUDIO-SMD_PJ-393,1,PJ-393_C2837065,C2837065
"C1, C12, C17, C188, C196, C2, C3, C34, C35, C36, C37, C38, C39, C7, C81",0402,15,2.2uF,
"C10, C11, C124, C126, C127, C13, C130, C133, C134, C138, C139, C14, C141, C147, C15, C150, C152, C153, C156, C158, C16, C163, C18, C198, C199, C200, C201, C202, C203, C206, C4, C40, C42, C43, C44, C45, C5, C50, C51, C52, C53, C54, C55, C59, C6, C60, C61, C62, C63, C75, C76, C79, C8, C80, C83, C84, C9",0402,57,0.1uF,
"C100, C140, C144, C145, C146, C151, C155, C159, C161, C164, C166, C172, C174, C175, C178, C78, C97, C98, C99",0402,19,100nF,
"C101, C102, C103, C104",CP_Radial_D8.0mm_P3.50mm,4,220uF,
"C105, C106, C107, C108",0603,4,680nF,
"C109, C110, C111, C112, C113, C114, C115, C116",0603,8,1uF,
"C117, C41",0603,2,0.1uF,
"C118, C119, C120, C121, C122, C123",0603,6,10nF,
C125,CP_Radial_D8.0mm_P2.50mm,1,2.2uF,
"C128, C136, C148",CP_Radial_D5.0mm_P2.00mm,3,1uF,
"C129, C132, C137",0402,3,10uF,
C131,CP_Radial_D5.0mm_P2.00mm,1,0.1uF,
"C142, C149",0402,2,220pF,
"C143, C160, C162, C167",CP_Radial_D8.0mm_P3.50mm,4,10uF,
"C154, C157",0402,2,22uF,
"C165, C189, C190, C191, C193, C194, C195, C197, C66, C67, C68, C69, C70, C71, C72, C73, C82",0402,17,1uF,
"C168, C169",0402,2,5.1pF,
"C170, C171",0402,2,5.6pF,
C173,0402,1,22pF,
"C176, C177, C179, C180, C181, C184",0603,6,10uF,
"C182, C183, C192",0603,3,220nF,
"C185, C186, C187, C89, C90, C91, C92, C93, C94, C95, C96",0402,11,220nF,
"C19, C20, C21, C22, C23, C24, C25, C26, C27, C28, C29, C30, C31, C32, C33",CAP-SMD_BD4.0-L4.3-W4.3-FD,15,10uF,
"C204, C205, C210",0402,3,47pF,
"C207, C208, C209",0603,3,47pF,
"C211, C212, C213, C214, C215, C216, C217, C218, C219, C220, C221, C222, C223, C224, C225, C226, C227, C228, C229, C230, C231, C232, C233, C234",0603,24,22uF,
"C46, C47",C_Rect_L4.0mm_W2.5mm_P2.50mm,2,82nF,
"C48, C49, C64, C65",C_Rect_L4.0mm_W2.5mm_P2.50mm,4,5.6nF,
"C56, C57",0603,2,82nF,
C58,0402,1,100uF,
C74,0402,1,10nF,
"C77, C85, C86, C87, C88",0402,5,1nF,
CARD1,TF-SMD_TF-PUSH,1,TF PUSH,C393941
CN2,CONN-TH_DIN-504B-M10,1,DIN-504B-M10,C2939346
"D1, D10, D11, D12, D13, D14, D15, D16, D17, D18, D19, D2, D20, D21, D22, D23, D24, D25, D26, D27, D28, D29, D3, D30, D31, D32, D33, D34, D35, D36, D37, D38, D39, D4, D40, D41, D42, D43, D44, D45, D46, D47, D48, D5, D6, D7, D8, D9",SOD-323_L1.8-W1.3-LS2.5-RD,48,1N4148WS_C917117,C917117
D49,LED0603-RD,1,LED,C5656657
D51,D_SOD-323_TVS,1,PESD15VL1BA,
"D52, D53, D54",0603,3,LED,
D55,SOT-23,1,BAT54,
FPC1,FPC-SMD_5034801200,1,5034801200,C587969
"J1, J2, J5",AUDIO-TH_PJ-625G,3,PJ-625G,C309300
"J10, J6",CONN-TH_B8PS-VH-LF-SN,2,Conn_01x08_Pin,C157970
"J11, J7, J8, J9",CONN-TH_2P-P5.00_WJ500V-5.08-2P,4,Conn_01x02_Socket,C8465
J3,PinHeader_1x13_P2.54mm_Vertical,1,Conn_01x13_Pin,
J4,PinHeader_1x03_P2.54mm_Vertical,1,Conn_01x03_Pin,
"L1, L2, L3, L4, L5, L6",IND-SMD_L11.0-W10.5_SL1050-330M,6,10uH,
L10,L1206,1,8uH,
"L11, L15",IND-SMD_L3.2-W2.5_L3225,2,6.8uH,
"L12, L13, L14",IND-SMD_L12.3-W12.3,3,15uH,
L7,IND-SMD_L4.8-W3.4,1,27uH,
L8,FILTER-SMD_4P-L0.9-W0.7-P0.50-BL,1,EXC14CE900U,C178761
L9,L_6.3x6.3_H3,1,6.8uH,
"Q1, Q2, Q3",Vishay_PowerPAK_1212-8_Single,3,Si7617DN,
"R1, R2, R3, R4, R5, R6",0402,6,470K,
"R10, R11, R19, R20, R24, R47, R48, R53, R55, R56, R57, R70, R71, R72, R9",0402,15,6K,
"R100, R101, R102, R103, R96, R97, R98, R99",0402,8,22,
"R104, R86",0402,2,1.5K,
"R105, R82",0402,2,0.01,
R106,0402,1,49.9,
R107,0402,1,50k,
R108,0402,1,2.61k,
"R109, R115, R116, R12, R13, R133, R135, R14, R15, R16, R17, R21, R22, R23, R25, R29, R30, R33, R34, R51, R52, R58, R59, R60, R61, R62, R63, R7, R79, R8, R92, R93, R94",0402,33,10k,
"R110, R112, R121, R123, R125, R127, R129, R131, R44, R45, R46, R49, R50, R74, R75, R78, R80, R89",0402,18,100K,
R111,0402,1,500K,
"R113, R114",0402,2,0,
"R117, R31, R32, R36, R37, R38, R39, R54, R77, R83, R87, R95",0402,12,1K,
R122,0402,1,24.9K,
"R124, R132",0402,2,43.2K,
"R126, R128, R130",0402,3,9.09K,
R134,0402,1,4.7k,
R18,0402,1,5K,
R26,0402,1,33,
"R28, R84",0402,2,10,
"R40, R42",0402,2,47k,
"R41, R43",0402,2,75k,
"R64, R65, R66, R67, R68, R69",0402,6,3.3,
R73,0402,1,2,
R76,0402,1,32.4K,
R81,0402,1,22.1K,
R85,0402,1,200K,
R88,0402,1,9.31K,
R90,R0603,1,NTCG163JF103FT1S,C406719
R91,0402,1,430K,
"SW1, SW11, SW12, SW13, SW14, SW15, SW16, SW17, SW18, SW2, SW21, SW22, SW23, SW24, SW25, SW26, SW27, SW28, SW29, SW3, SW30, SW31, SW32, SW35, SW36, SW37, SW38, SW39, SW4, SW40, SW41, SW42, SW43, SW44, SW45, SW46, SW47, SW48, SW49, SW50, SW51, SW52, SW53, SW54, SW55, SW56, SW57, SW6, SW7, SW8, SW9",SW-SMD_4P-L12.0-W12.0-P5.00-LS15.4,51,TS-1003ST-26,C455234
"SW10, SW19, SW20, SW33, SW34, SW5",SW-TH_EC12EXXXX,6,RotaryEncoder,C470684
"SW58, SW60",SW_SPST_CK_RS282G05A3,2,SW_Push,
SW59,SW-TH_EC11E1820402,1,RotaryEncoder_Switch,C361165
"U1, U2, U3",TSSOP-28_4.4x9.7mm_P0.65mm,3,PCM5122PW,
"U10, U12, U13, U14, U9",SW-TH_6P-L7.0-W7.0-P2.00_7-7-ZS,5,~,C5379891
"U11, U16, U20, U23, U4, U5, U6, U7, U8",SOIC-8_L4.9-W3.9-P1.27-LS6.0-BL,9,NE5532DR,C7426
U15,UQFN-10_L2.0-W1.5-P0.50-BL-EP,1,TS5A23159RSER,C138710
U17,HSOP-20_L12.8-W7.5-P1.27-LS10.3-BL-EP3.3,1,TPA6120A2DWP,C2871054
"U18, U19",HTSSOP-32_L11.0-W6.1-P0.65-LS8.1-BL,2,TPA3116D2DAD_C2865736,C2865736
U21,QFN-24_L4.0-W4.0-P0.50-BL-EP2.6,1,CY8CMBR3116-LQXIT,C914913
"U22, U24",FPC-SMD_6P-P0.50_XUNPU_FPC-05F-6PH20,2,FPC-05F-6PH20,C2856796
U25,VQFN-24-1EP_4x4mm_P0.5mm_EP2.45x2.45mm,1,BQ24610,
U26,SOT-23-6,1,TPS54202DDC,
U27,TSOP-48_L12.0-W18.4-P0.50-LS20.0-TL,1,W29N02KVSIAF,C2940193
U28,SOT-666,1,USBLC6-2P6,
U29,DSBGA-9_L1.4-W1.3-R3-C3-P0.40-BL,1,TUSB422IYFPR,C702378
"U30, U31",PDFN-8_L3.1-W3.1-P0.65-LS3.4-BL,2,SIS412DN-T1-GE3-ES,C21713860
U32,CRYSTAL-SMD_4P-L3.2-W2.5-BL_SIT8008BI,1,~,C7294602
U33,OLED-SMD_HS20HS072RX,1,HS20HS072RX,C5329582
"U34, U35, U36, U37, U38, U39",ESOP-8_L4.9-W3.9-P1.27-LS6.0-TL-EP,6,LMR33630ADDAR,C841384
USB1,USB-C-SMD_TYPE-C-6PIN-2MD-073,1,TYPE-C 16PIN 2MD(073),C2765186
VQ1,LQFP-144_L20.0-W20.0-P0.50-LS22.0-BL,1,STM32H723ZGT6,C730146
Y1,FC-135R_L3.2-W1.5,1,32.768KHz,

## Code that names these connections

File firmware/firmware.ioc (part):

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Mcu.Name=STM32H723ZGTx
Mcu.Package=LQFP144
Mcu.UserName=STM32H723ZGTx
PA0.Mode=Asynchronous
PA0.Signal=UART4_TX
PA1.Mode=Asynchronous
PA1.Signal=UART4_RX
PA10.Signal=GPXTI10
PA11.Mode=Host_FS
PA11.Signal=USB_OTG_HS_DM
PA12.Mode=Host_FS
PA12.Signal=USB_OTG_HS_DP
PA15(JTDI).Mode=Half_Duplex_Master_Tx
PA15(JTDI).Signal=I2S1_WS
PA4.Mode=Half_Duplex_Master_Tx
PA4.Signal=I2S3_WS
PA5.Mode=Half_Duplex_Master_Tx
PA5.Signal=I2S1_CK
PA7.Mode=Half_Duplex_Master_Tx
PA7.Signal=I2S1_SDO
PA9.Mode=Activate_VBUS_FS
PA9.Signal=USB_OTG_HS_VBUS
PB10.Mode=Half_Duplex_Master_Tx
PB10.Signal=I2S2_CK
PB12.Mode=Half_Duplex_Master_Tx
PB12.Signal=I2S2_WS
PB13.Mode=SD_4_bits_Wide_bus
PB13.Signal=SDMMC1_D0
PB2.Mode=Half_Duplex_Master_Tx
PB2.Signal=I2S3_SDO
PB3(JTDO/TRACESWO).Mode=Half_Duplex_Master_Tx
PB3(JTDO/TRACESWO).Signal=I2S3_CK
PB6.Mode=SMBus-two-wire-Interface
PB6.Signal=I2C1_SCL
PB7.Mode=SMBus-two-wire-Interface
PB7.Signal=I2C1_SDA
PC1.Mode=Half_Duplex_Master_Tx
PC1.Signal=I2S2_SDO
PC10.Mode=SD_4_bits_Wide_bus
PC10.Signal=SDMMC1_D2
PC11.Mode=SD_4_bits_Wide_bus
PC11.Signal=SDMMC1_D3
PC12.Mode=SD_4_bits_Wide_bus
PC12.Signal=SDMMC1_CK
PC14-OSC32_IN.Mode=LSE-External-Oscillator
PC14-OSC32_IN.Signal=RCC_OSC32_IN
PC15-OSC32_OUT.Mode=LSE-External-Oscillator
PC15-OSC32_OUT.Signal=RCC_OSC32_OUT
PC6.Signal=FMC_NWAIT
PC8.Mode=NandChipSelect3_1
PC8.Signal=FMC_NCE
PC9.Mode=SD_4_bits_Wide_bus
PC9.Signal=SDMMC1_D1
PD0.Signal=FMC_D2_DA2
PD1.Signal=FMC_D3_DA3
PD11.Signal=FMC_A16_CLE
PD12.Signal=FMC_A17_ALE
PD14.Signal=FMC_D0_DA0
PD15.Signal=FMC_D1_DA1
PD2.Mode=SD_4_bits_Wide_bus
PD2.Signal=SDMMC1_CMD
PD4.Signal=FMC_NOE
PD5.Signal=FMC_NWE
PE10.Signal=FMC_D7_DA7
PE2.Mode=Simplex_Bidirectional_Master
PE2.Signal=SPI4_SCK
PE4.Mode=NSS_Signal_Hard_Output
PE4.Signal=SPI4_NSS
PE6.Mode=Simplex_Bidirectional_Master
PE6.Signal=SPI4_MOSI
PE7.Signal=FMC_D4_DA4
PE8.Signal=FMC_D5_DA5
PE9.Signal=FMC_D6_DA6
PF0.Mode=I2C
PF0.Signal=I2C2_SDA
PF1.Mode=I2C
PF1.Signal=I2C2_SCL
PF14.Mode=I2C
PF14.Signal=I2C4_SCL
PF15.Mode=I2C
PF15.Signal=I2C4_SDA
PH0-OSC_IN.Mode=HSE-External-Oscillator
PH0-OSC_IN.Signal=RCC_OSC_IN
PH1-OSC_OUT.Mode=HSE-External-Oscillator
PH1-OSC_OUT.Signal=RCC_OSC_OUT
RCC.SYSCLKFreq_VALUE=64000000
board=custom

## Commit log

2025-07-07 hardware
2025-07-27 jjjjjjjjjjjjj
2025-07-30 yess
2025-07-30 yesss
2025-08-01 ñushsh
2025-08-16 added stuff
2025-08-20 yeesss
